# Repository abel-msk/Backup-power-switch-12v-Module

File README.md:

# Power backup board

12 V power switch with a 3S Li-ion backup. Loads run from the 12 V PSU and
switch to the battery when mains power is lost. An ESP32-C3 monitors voltages
and currents and controls the switchover.

## How it works

- **Switchover:** relay K1 (SRD-12VDC, driven by the ESP32-C3 through Q3 BSS138)
  selects PSU or battery for the outputs. Diode-OR D7 (MBRF3045CT) keeps the
  outputs powered while the relay changes over.
- **Reverse-current guard:** LM74700-Q1 (U9) with IRLR7843 (Q4) acts as an ideal
  diode on the battery leg. It stops the PSU from pushing current into the pack
  through the relay.
- **Charger:** CN3763 (U6) buck charger for a 3S pack with BMS, 1.2 A charge
  current (Rcs2 = 0.1 Ohm).
- **Monitoring:** two INA219 sensors on I2C: U2 (0x40) measures PSU current,
  U3 (0x45) measures battery current. 51k/10k dividers feed the PSU voltage
  (A0, GPIO0) and the battery voltage (A1, GPIO1) to the ADC.
- **Logic supply:** AMS1117-3.3 (U8). J9 selects its input source.

## Connectors

| Ref | Function |
|---|---|
| J1 | Screw terminal: battery and PSU inputs |
| J3 | Screw terminal: 12 V output |
| J4, J6, J7, J8 | 4x barrel jack 12 V outputs |
| J5 | External: GND, 3V3, SCL, SDA, A0, A1, DONE, CHRG |
| J2 | Display/UART: SPI (SCK, MOSI, MISO, SS), TX, RX, 3V3, GND |
| J9 | Logic supply selector |

## Versions

First version

Version v3.1

Current version v5.0

## Known issues and limitations (v5.0)

### Battery is not charged to 100 %

The CN3763 charger (U6) is a buck converter with a maximum duty cycle of 94 %,
so the pack voltage can never reach the charger input voltage. After the
losses in D3, Rcs2, Q2 and L2 the reachable pack voltage is roughly:

| PSU voltage | Pack voltage | Per cell | Usable capacity |
|---|---|---|---|
| 12.0 V | ~10.9 V | ~3.6 V | ~20-30 % |
| **12.6 V (recommended)** | **~11.2-11.4 V** | **~3.75-3.8 V** | **~45-55 %** |
| 13.2 V | ~11.7-11.9 V | ~3.9 V | ~60-70 % |

A full charge (12.6 V, 4.2 V/cell) needs about 14.1 V at the charger input.

Consequences:
- The charger never enters constant-voltage mode, so **DONE is never asserted**.
  D1 (DONE LED) and U5 (DONE optocoupler) are marked **DNP**.
- **CHRG stays on** (LED D5 lit, CHRG_SIG low) whenever the PSU is present.
  It means "PSU present, charger running", not "battery charging".
- Partial charge extends battery life considerably: calendar ageing at
  3.8 V/cell is much slower than at 4.2 V/cell.
- Most BMS boards balance only near 4.15-4.2 V/cell, so **cell balancing is not
  active**. Check individual cell voltages every few months.

Possible future fix: feed only the charger (U6 VCC, Q2 source, C6, C9) from a
separate 12 V to 15 V boost module (XL6019/XL6009 for 1.2 A charge current;
MT3608 only with Rcs2 = 0.2 Ohm, i.e. 0.6 A). The boost output must not be tied
to PWR OUT 12 +, otherwise 15 V reaches the loads through K1/D7.

### PSU voltage

Set the PSU to **12.6 V** (13.2 V maximum). Do not go higher: the outputs feed
12 V loads, and the AMS1117 (U8) is limited to 15 V input.

### Firmware notes

- Charge status: use the battery current from U3 (INA219, 0x45) and the pack
  voltage, not CHRG_SIG / DONE_SIG.
  - current into the pack > ~50-100 mA: charging;
  - ~0 A with PSU present: pack has reached its (partial) charge limit;
  - current out of the pack: running on battery.
- Low-voltage cutoff: drop the load at about **9.9 V (3.3 V/cell)**.
  The BMS only disconnects at 2.5-3.0 V/cell.
- GPIO2 is an ESP32-C3 strapping pin. It carries DONE_SIG and is pulled high
  by R19. **Do not populate U5**: it would pull GPIO2 low at reset and the ESP
  could fail to boot.
- Mains loss with the relay in the PSU position: the battery back-feeds
  PWR OUT / PWR IN through D7 and K1 NO, so the A0 divider still reads a near
  normal voltage. Detect mains loss by current instead (U2 current drops to ~0
  or goes negative, U3 shows discharge) and switch K1 to the battery.

### Other

- U8 AMS1117-3.3 dissipates about 0.9 W at 12.6 V input. The tab is VOUT
  (+3V3), not GND.
- Charge current is set by Rcs2: Ich = 120 mV / Rcs2 = 1.2 A with 0.1 Ohm.
- KiCad 10.0.x: writing to the board through the IPC API (BeginCommit) can
  crash KiCad when the schematic editor is loaded. Use the API read-only or
  open only the PCB editor.

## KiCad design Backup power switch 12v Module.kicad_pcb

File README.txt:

# Power backup board

Board for 12v power switch.  Plain power and battery backup.  Switchng provided by LM393 comparator. Both compared   line are adjustable by potentiometer.
Equipped with:
Battery 3S charger, 
Two INA219 i2c sensors
ESP32-C3 wifi board
Charge and done charger passed to ESP
External connector for i2x line and charger status

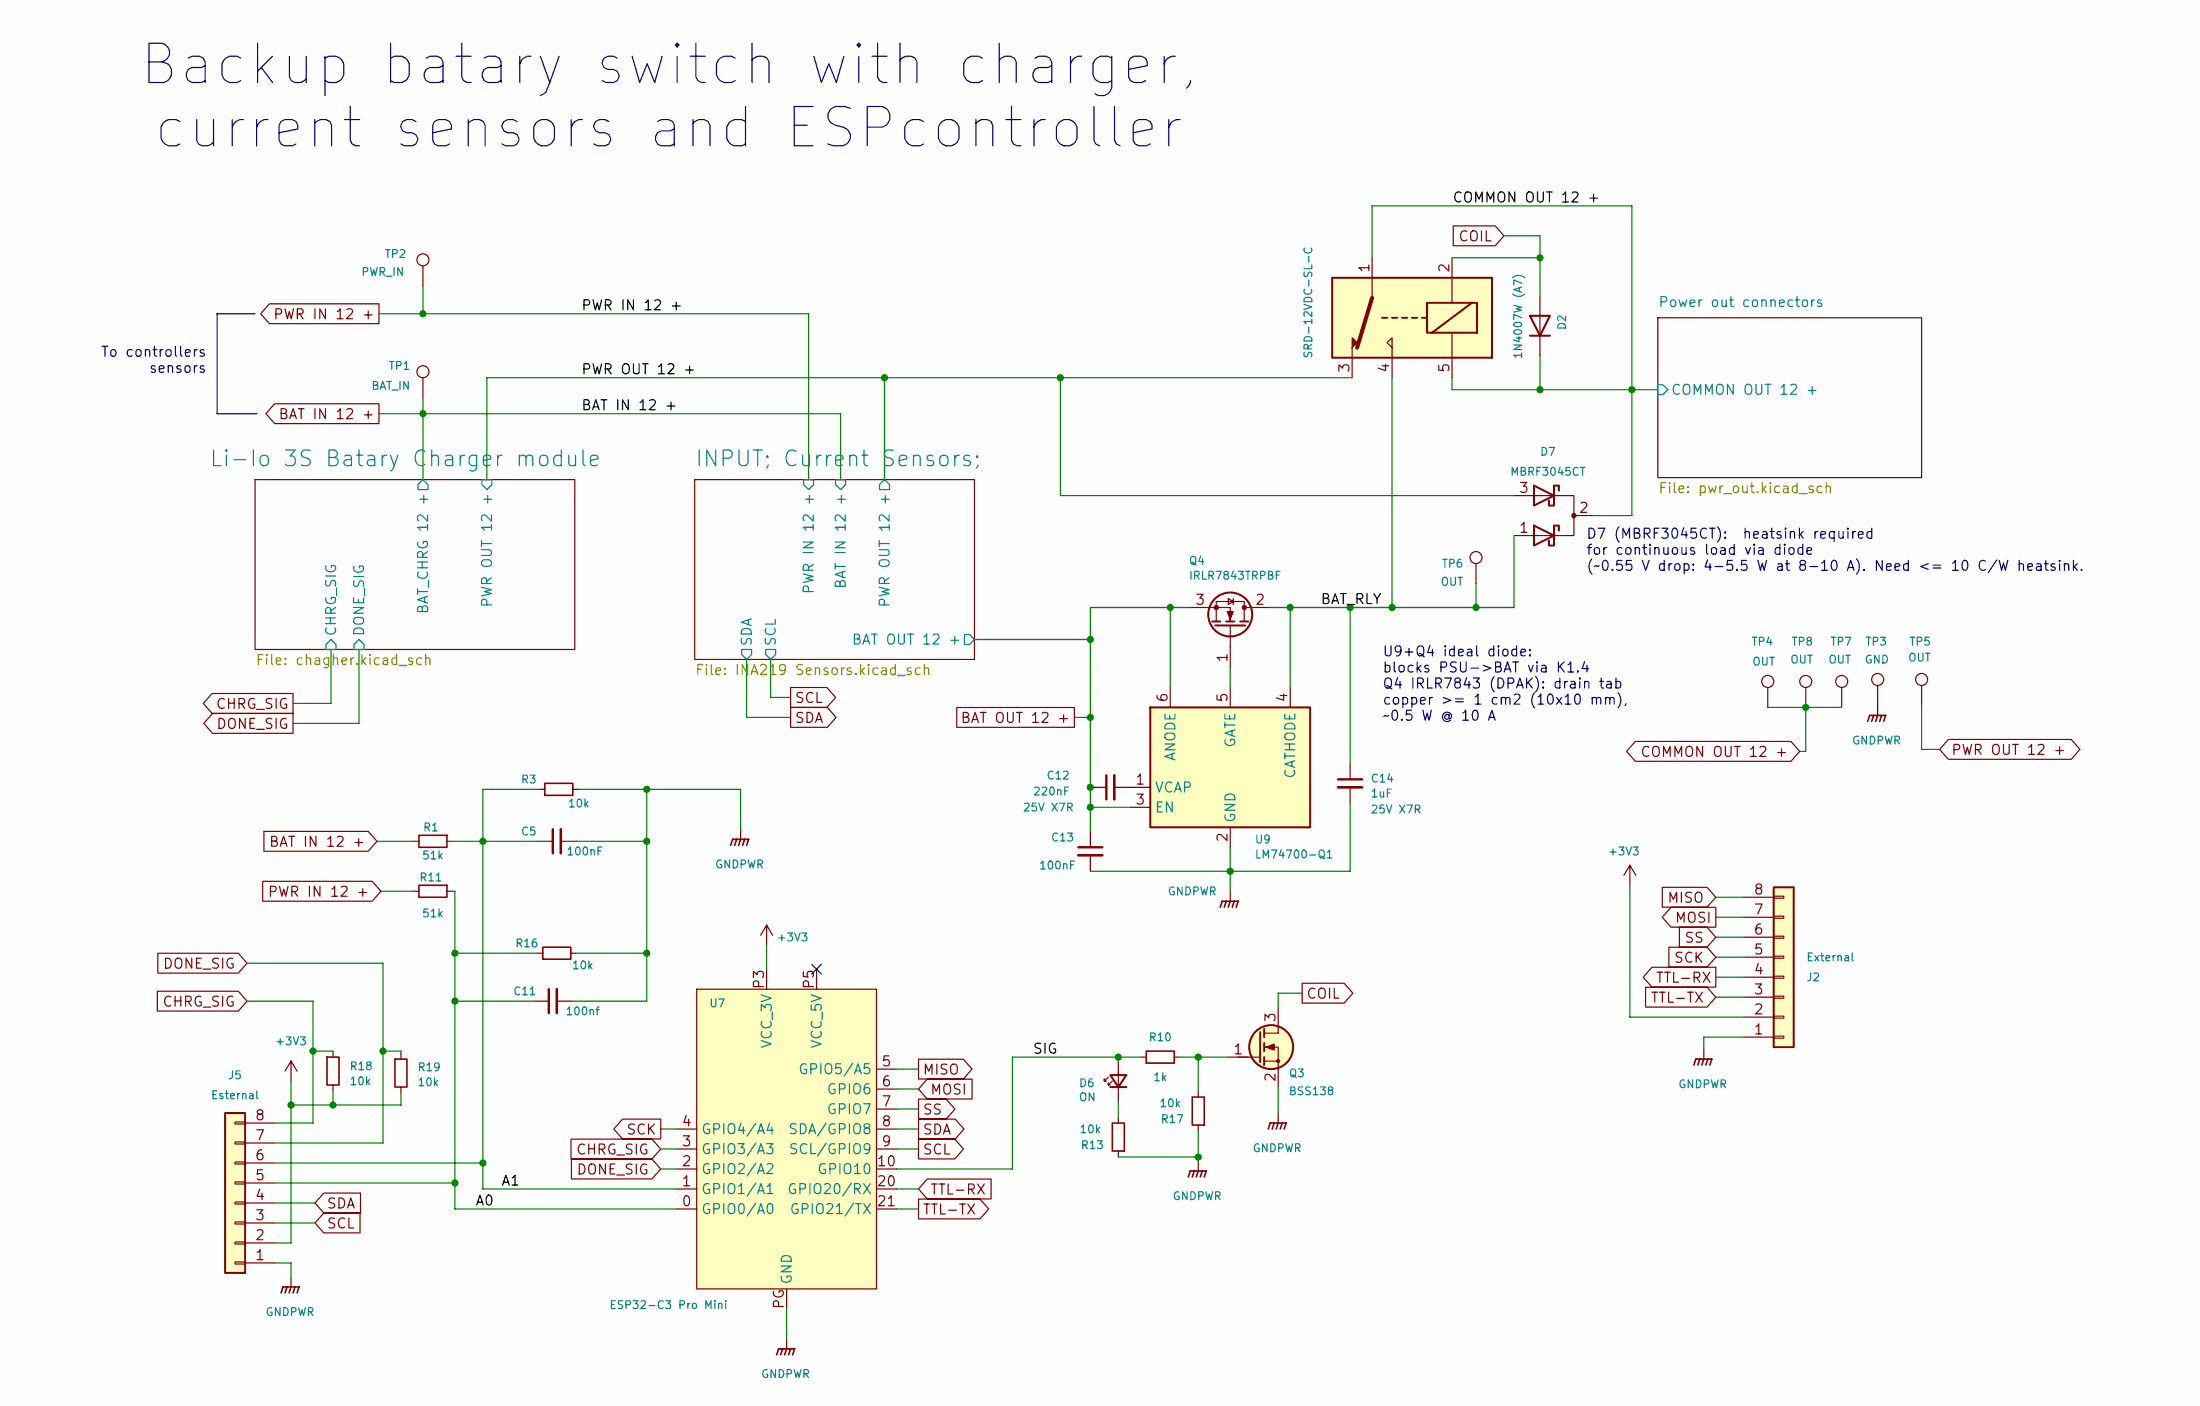
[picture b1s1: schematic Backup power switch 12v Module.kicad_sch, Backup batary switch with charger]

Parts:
C5, C13: 100nF; C_0805_2012Metric_Pad1.18x1.45mm_HandSolder
C11: 100nf; C_0805_2012Metric_Pad1.18x1.45mm_HandSolder
C12: 220nF; C_0805_2012Metric_Pad1.18x1.45mm_HandSolder
C14: 1uF; C_0805_2012Metric_Pad1.18x1.45mm_HandSolder
D2: 1N4007W (A7); D_SMA
D6: ON; LED_0603_1608Metric_Pad1.05x0.95mm_HandSolder
D7: MBRF3045CT; TO-220-3_Staggered_Vertical
J2: External; JST_PH_B8B-PH-K_1x08_P2.00mm_Vertical
J5: Esternal; JST_PH_B8B-PH-K_1x08_P2.00mm_Vertical
K1: SRD-12VDC-SL-C; Relay_SPDT_SANYOU_SRD_Series_Form_C
Q3: BSS138; SOT-23-3
Q4: IRLR7843TRPBF; TO-252-2; MPN IRLR7843TRPBF
R1, R11: 51k; R_0805_2012Metric_Pad1.20x1.40mm_HandSolder
R3, R13, R16, R17, R18, R19: 10k; R_0805_2012Metric_Pad1.20x1.40mm_HandSolder
R10: 1k; R_0805_2012Metric_Pad1.20x1.40mm_HandSolder
TP1: BAT_IN; TestPoint_Loop_D2.50mm_Drill1.85mm
TP2: PWR_IN; TestPoint_Loop_D2.50mm_Drill1.85mm
TP3: GND; TestPoint_Loop_D2.50mm_Drill1.85mm
TP4, TP5, TP6, TP7, TP8: OUT; TestPoint_Loop_D2.50mm_Drill1.85mm
U7: ESP32-C3 Pro Mini; ESP32-C3_Pro_mini_pin
U9: LM74700-Q1; SOT-23-6; MPN LM74700QDBVRQ1

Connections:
+3V3: J2.2, J5.2, R18.2, R19.2, U7.P3 (VCC_3V); also elsewhere on the board
/A0: C11.1, J5.5, R11.1, R16.1, U7.0 (GPIO0/A0)
/A1: C5.1, J5.6, R1.1, R3.1, U7.1 (GPIO1/A1)
/BAT_RLY: C14.1, D7.1 (A1), K1.4, Q4.2 (D), TP6.1 (1_1), U9.4 (CATHODE)
/SIG: D6.2 (A), R10.1, U7.10 (GPIO10)
BAT IN 12 +: R1.2, TP1.1 (1_1); also elsewhere on the board
BAT OUT 12 +: C12.1, C13.1, Q4.3 (S), U9.3 (EN), U9.6 (ANODE); also elsewhere on the board
CHRG_SIG: J5.8, R18.1, U7.3 (GPIO3/A3); also elsewhere on the board
COIL: D2.2 (A), K1.2, Q3.3 (D)
COMMON OUT 12 +: D2.1 (K), D7.2 (K), K1.1, K1.5, TP4.1 (1_1), TP7.1 (1_1), TP8.1 (1_1); also elsewhere on the board
DONE_SIG: J5.7, R19.1, U7.2 (GPIO2/A2); also elsewhere on the board
GNDPWR: C5.2, C11.2, C13.2, C14.2, J2.1, J5.1, Q3.2 (S), R3.2, R13.1, R16.2, R17.1, TP3.1 (1_1), U7.PG (GND), U9.2 (GND); also elsewhere on the board
MISO: J2.8, U7.5 (GPIO5/A5)
MOSI: J2.7, U7.6 (GPIO6)
unnamed: D6.1 (K), R13.2
unnamed: Q3.1 (G), R10.2, R17.2
unnamed: Q4.1 (G), U9.5 (GATE)
unnamed: C12.2, U9.1 (VCAP)
PWR IN 12 +: R11.2, TP2.1 (1_1); also elsewhere on the board
PWR OUT 12 +: D7.3 (A2), K1.3, TP5.1 (1_1); also elsewhere on the board
SCK: J2.5, U7.4 (GPIO4/A4)
SCL: J5.3, U7.9 (SCL/GPIO9); also elsewhere on the board
SDA: J5.4, U7.8 (SDA/GPIO8); also elsewhere on the board
SS: J2.6, U7.7 (GPIO7)
TTL-RX: J2.4, U7.20 (GPIO20/RX)
TTL-TX: J2.3, U7.21 (GPIO21/TX)

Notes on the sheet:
Backup batary switch with charger, current sensors and ESPcontroller
U9+Q4 ideal diode: blocks PSU->BAT via K1.4 Q4 IRLR7843 (DPAK): drain tab copper >= 1 cm2 (10x10 mm), ~0.5 W @ 10 A
D7 (MBRF3045CT): heatsink required for continuous load via diode (~0.55 V drop: 4-5.5 W at 8-10 A). Need <= 10 C/W heatsink.
To controllers sensors

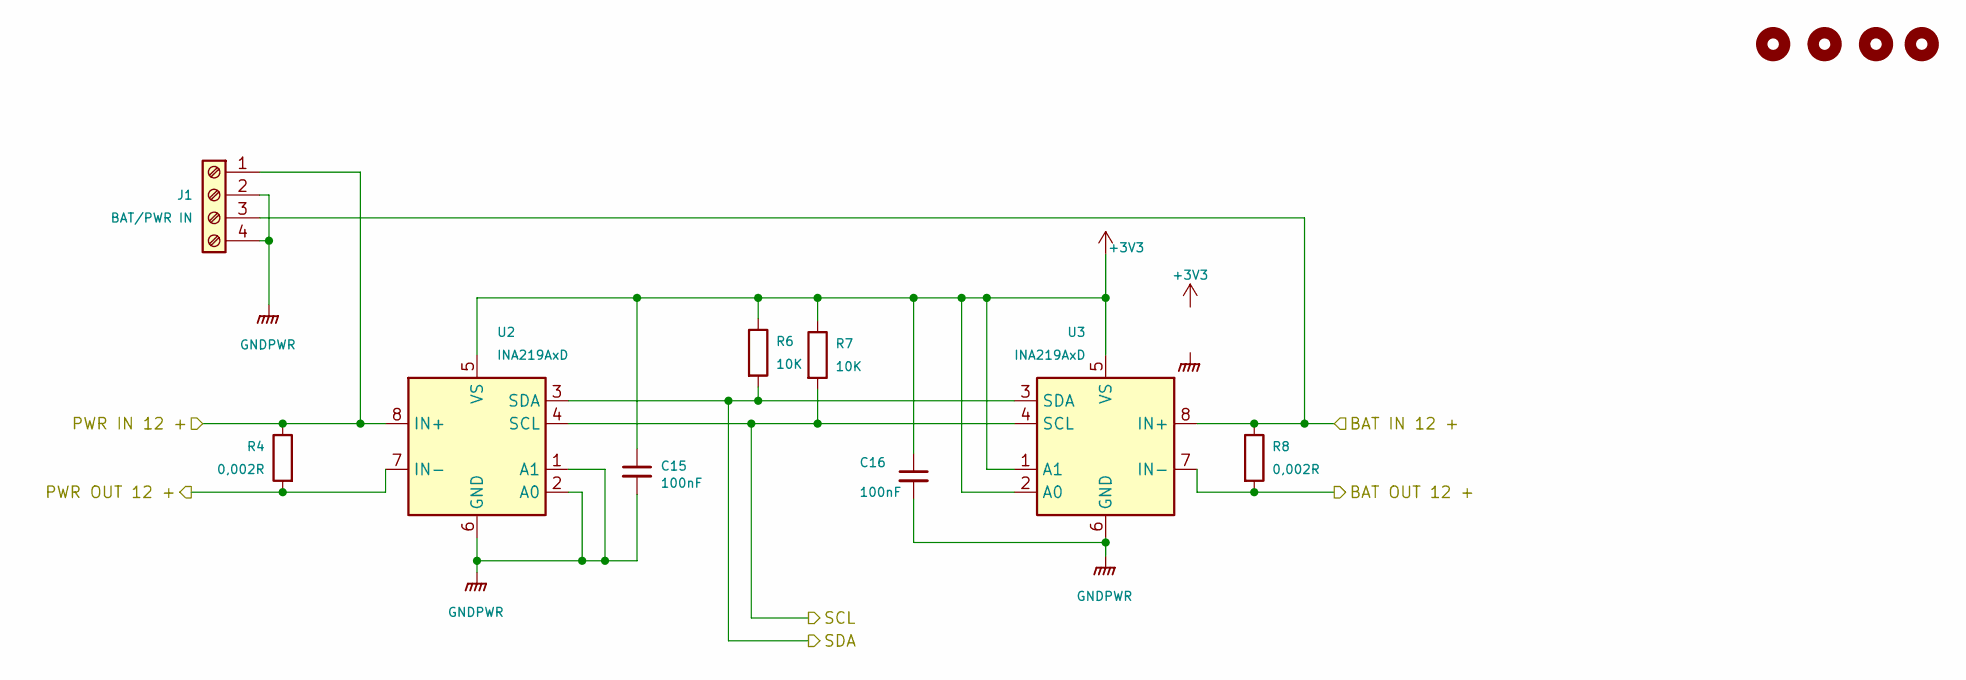
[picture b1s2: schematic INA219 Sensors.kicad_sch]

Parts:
C15, C16: 100nF; C_0805_2012Metric_Pad1.18x1.45mm_HandSolder
H1, H2, H3, H4: MountingHole; MountingHole_3.5mm_Pad_TopBottom
J1: BAT/PWR IN; ScrewTerminal_KF7.62_4P
R4, R8: 0,002R; R_2512_6332Metric_Pad1.40x3.35mm_HandSolder
R6, R7: 10K; R_0805_2012Metric_Pad1.20x1.40mm_HandSolder
U2, U3: INA219AxD; SOIC-8_3.9x4.9mm_P1.27mm

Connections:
+3V3: C15.1, C16.1, R6.1, R7.1, U2.5 (VS), U3.1 (A1), U3.2 (A0), U3.5 (VS); also elsewhere on the board
BAT IN 12 +: J1.3, R8.1, U3.8 (IN+); also elsewhere on the board
BAT OUT 12 +: R8.2, U3.7 (IN-); also elsewhere on the board
GNDPWR: C15.2, C16.2, J1.2, J1.4, U2.1 (A1), U2.2 (A0), U2.6 (GND), U3.6 (GND); also elsewhere on the board
PWR IN 12 +: J1.1, R4.1, U2.8 (IN+); also elsewhere on the board
PWR OUT 12 +: R4.2, U2.7 (IN-); also elsewhere on the board
SCL: R7.2, U2.4 (SCL), U3.4 (SCL); also elsewhere on the board
SDA: R6.2, U2.3 (SDA), U3.3 (SDA); also elsewhere on the board

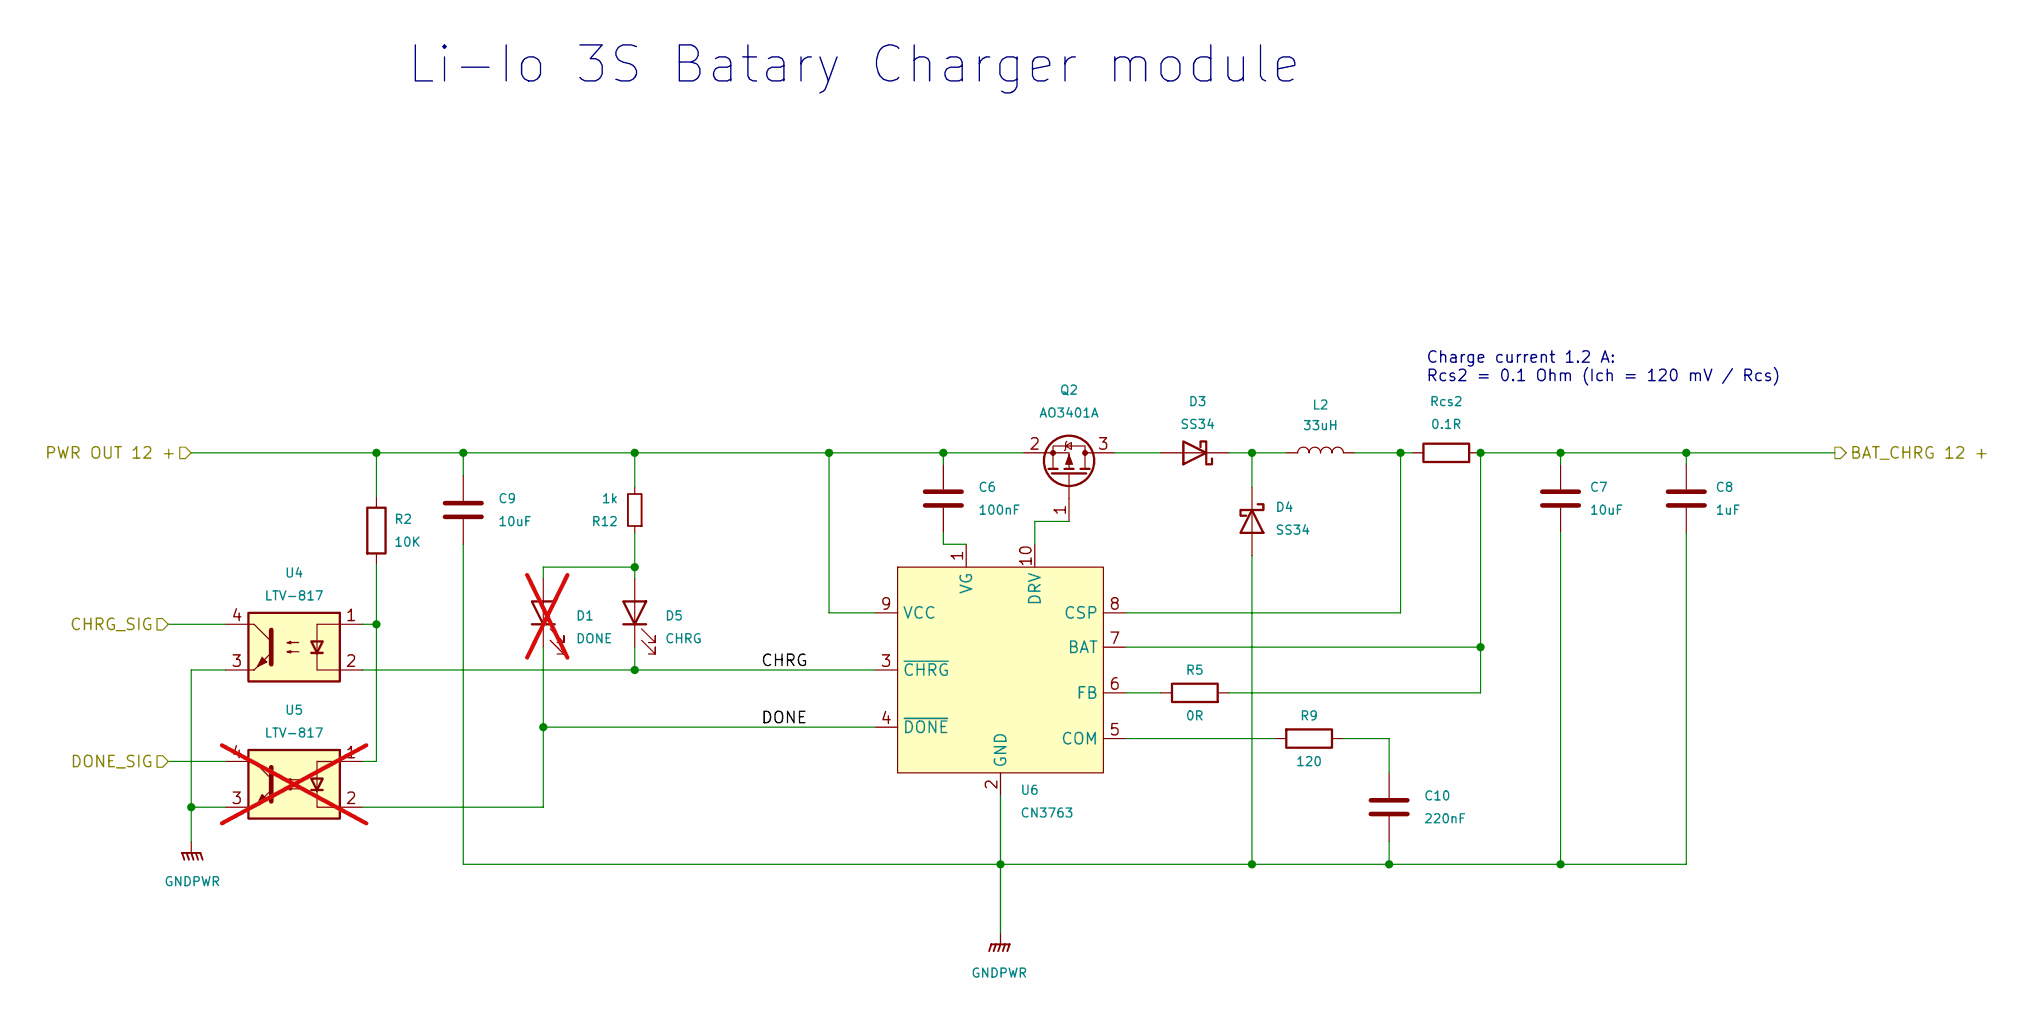
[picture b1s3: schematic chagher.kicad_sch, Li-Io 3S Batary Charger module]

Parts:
C6: 100nF; C_0805_2012Metric_Pad1.18x1.45mm_HandSolder
C7, C9: 10uF; C_1210_3225Metric_Pad1.33x2.70mm_HandSolder
C8: 1uF; C_0805_2012Metric_Pad1.18x1.45mm_HandSolder
C10: 220nF; C_0805_2012Metric_Pad1.18x1.45mm_HandSolder
D1: DONE; LED_0603_1608Metric_Pad1.05x0.95mm_HandSolder; not fitted
D3: SS34; D_SMA
D4: SS34; D_SMA; MPN SS34
D5: CHRG; LED_0603_1608Metric_Pad1.05x0.95mm_HandSolder
L2: 33uH; L_Bourns-SRN8040_8x8.15mm; MPN SRN8040-330M
Q2: AO3401A; SOT-23
R2: 10K; R_0805_2012Metric_Pad1.20x1.40mm_HandSolder
R5: 0R; R_0805_2012Metric_Pad1.20x1.40mm_HandSolder
R9: 120; R_0805_2012Metric_Pad1.20x1.40mm_HandSolder
R12: 1k; R_0805_2012Metric_Pad1.20x1.40mm_HandSolder
Rcs2: 0.1R; R_2512_6332Metric_Pad1.40x3.35mm_HandSolder
U4: LTV-817; DIP-4_W7.62mm
U5: LTV-817; DIP-4_W7.62mm; not fitted
U6: CN3763; SSOP-10_3.9x4.9mm_P1.00mm

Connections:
/Li-Io 3S Batary Charger module/CHRG: D5.1 (K), U4.2, U6.3 (~CHRG)
/Li-Io 3S Batary Charger module/DONE: D1.1 (K), U5.2, U6.4 (~DONE)
BAT IN 12 +: C7.1, C8.1, R5.2, Rcs2.2, U6.7 (BAT); also elsewhere on the board
CHRG_SIG: U4.4; also elsewhere on the board
DONE_SIG: U5.4; also elsewhere on the board
GNDPWR: C7.2, C8.2, C9.2, C10.2, D4.2 (A), U4.3, U5.3, U6.2 (GND); also elsewhere on the board
unnamed: C10.1, R9.1
unnamed: D1.2 (A), D5.2 (A), R12.1
unnamed: D3.2 (A), Q2.3 (D)
unnamed: D3.1 (K), D4.1 (K), L2.1
unnamed: Q2.1 (G), U6.10 (DRV)
unnamed: R2.2, U4.1, U5.1
unnamed: R9.2, U6.5 (COM)
unnamed: L2.2, Rcs2.1, U6.8 (CSP)
unnamed: R5.1, U6.6 (FB)
unnamed: C6.2, U6.1 (VG)
PWR OUT 12 +: C6.1, C9.1, Q2.2 (S), R2.1, R12.2, U6.9 (VCC); also elsewhere on the board

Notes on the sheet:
Charge current 1.2 A: Rcs2 = 0.1 Ohm (Ich = 120 mV / Rcs)
Li-Io 3S Batary Charger module

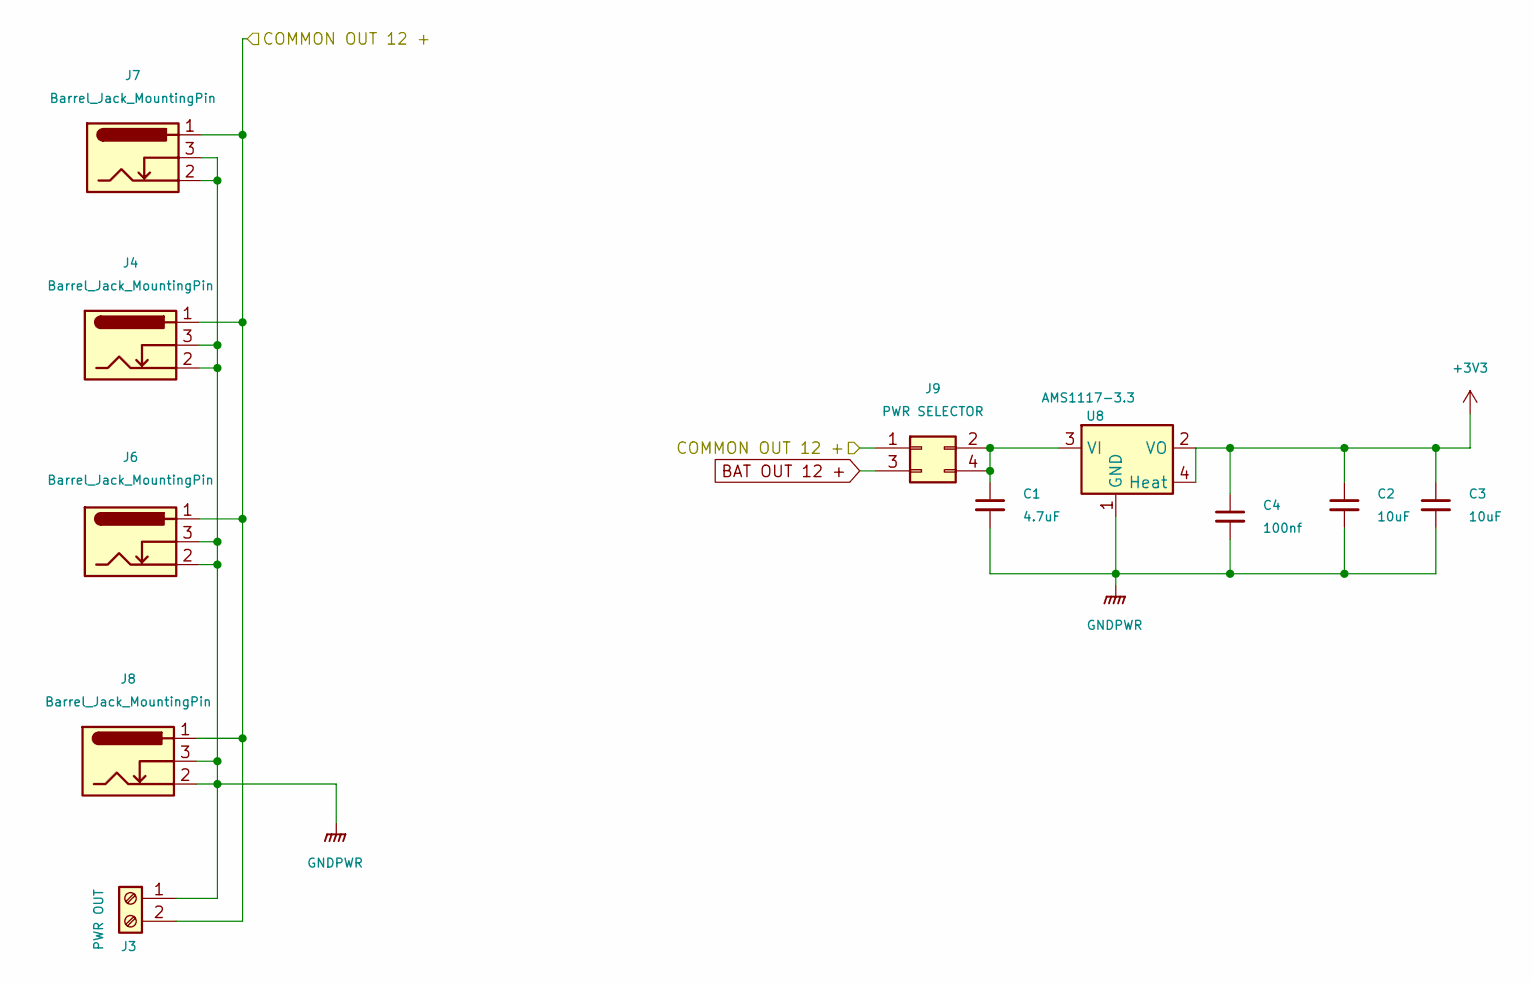
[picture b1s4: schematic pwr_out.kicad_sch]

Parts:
C1: 4.7uF; C_1206_3216Metric_Pad1.33x1.80mm_HandSolder
C2, C3: 10uF; CP_EIA-3528-21_Kemet-B_HandSolder
C4: 100nf; C_0805_2012Metric_Pad1.18x1.45mm_HandSolder
J3: PWR OUT; ScrewTerminal_KF7.62_2P
J4, J6, J7, J8: Barrel_Jack_MountingPin; BarrelJack_Horizontal
J9: PWR SELECTOR; PinHeader_2x02_P2.54mm_Vertical
U8: AMS1117-3.3; SOT-223

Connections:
+3V3: C2.1, C3.1, C4.1, U8.2 (VO), U8.4 (Heat); also elsewhere on the board
BAT OUT 12 +: J9.3; also elsewhere on the board
COMMON OUT 12 +: J3.2, J4.1, J6.1, J7.1, J8.1, J9.1; also elsewhere on the board
GNDPWR: C1.2, C2.2, C3.2, C4.2, J3.1, J4.2, J4.3, J6.2, J6.3, J7.2, J7.3, J8.2, J8.3, U8.1 (GND); also elsewhere on the board
unnamed: C1.1, J9.2, J9.4, U8.3 (VI)

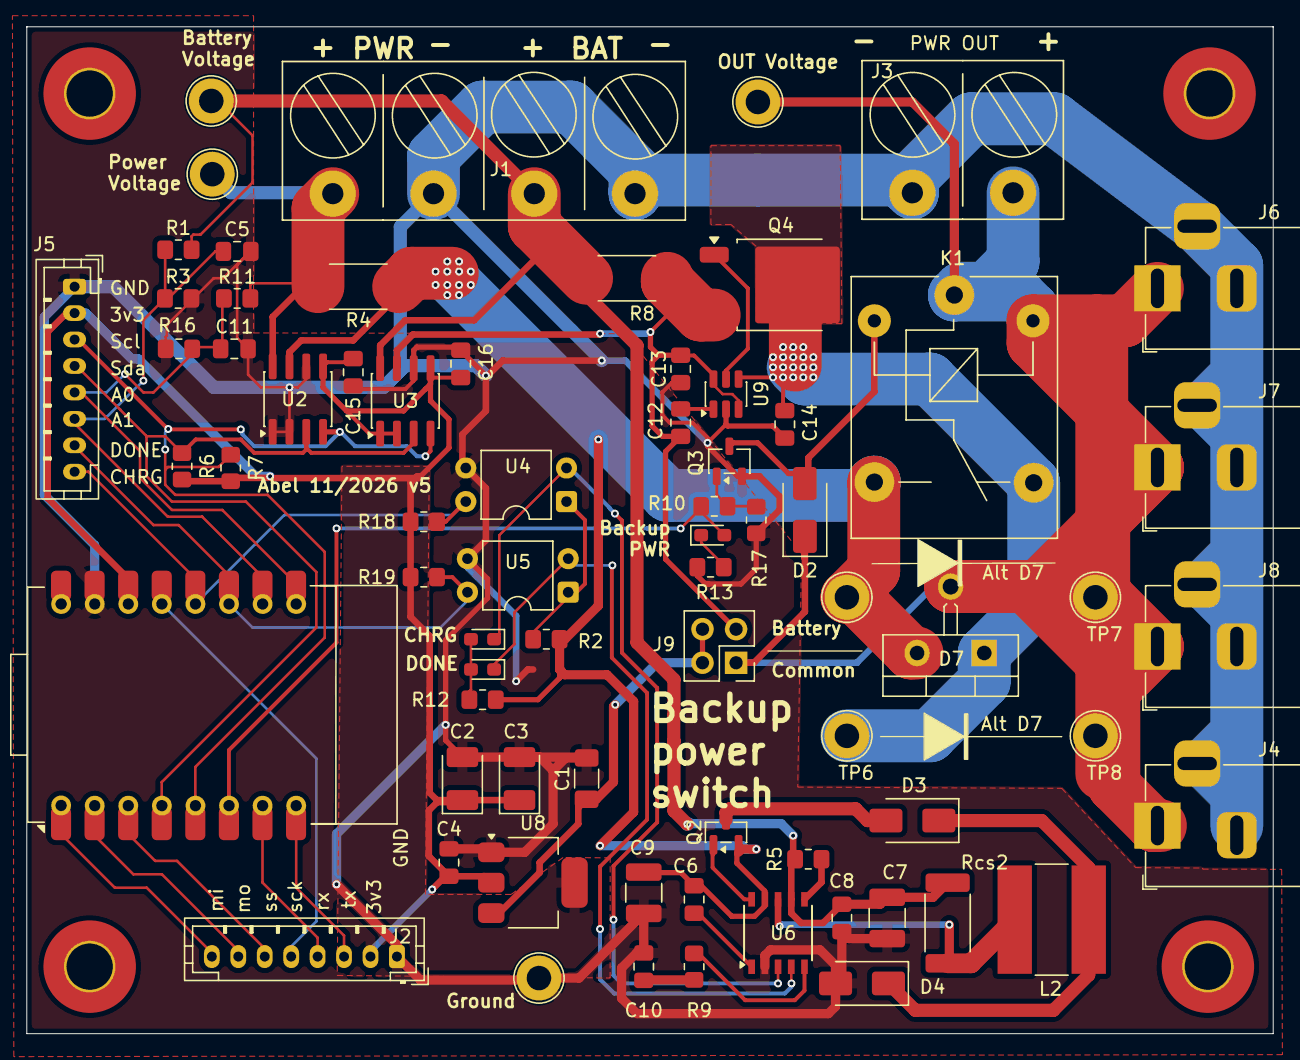
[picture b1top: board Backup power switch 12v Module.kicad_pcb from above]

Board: 2 copper layers, 94.3 x 76.2 mm, 75 parts (0 on the bottom side), 39 nets.

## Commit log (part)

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2026-01-16 Fist release
2026-01-16 add descr
2026-01-16 Rename README.txt to README.mdfix readme
2026-01-16 Fix image path for 3D view in README
    Updated the image path for the 3D view in the README.
2026-01-17 DRC check
2026-02-08 Add bat input stabilizer
2026-02-08 add stab scheme
2026-02-08 Fix comparator out signal pullup
2026-02-12 Some sheme clarify
2026-02-14 Add power sockwr
2026-02-28 Clean space for second relay
2026-02-28 Place second relay
2026-03-01 Connect srcond relay
2026-03-01 Fix charger in/out nammes
2026-03-01 Production
2026-03-02 Some fixes
2026-03-29 Add poert switch
2026-04-19 Move to kikad10
2026-05-02 Add more space aroung relay
2026-05-02 Add holes for alt diodes. Prod. Docs
2026-06-14 add info
2026-06-14 Fix info
